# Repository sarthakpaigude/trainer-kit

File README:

This contains all Proteus and KiCad files for entire Project.

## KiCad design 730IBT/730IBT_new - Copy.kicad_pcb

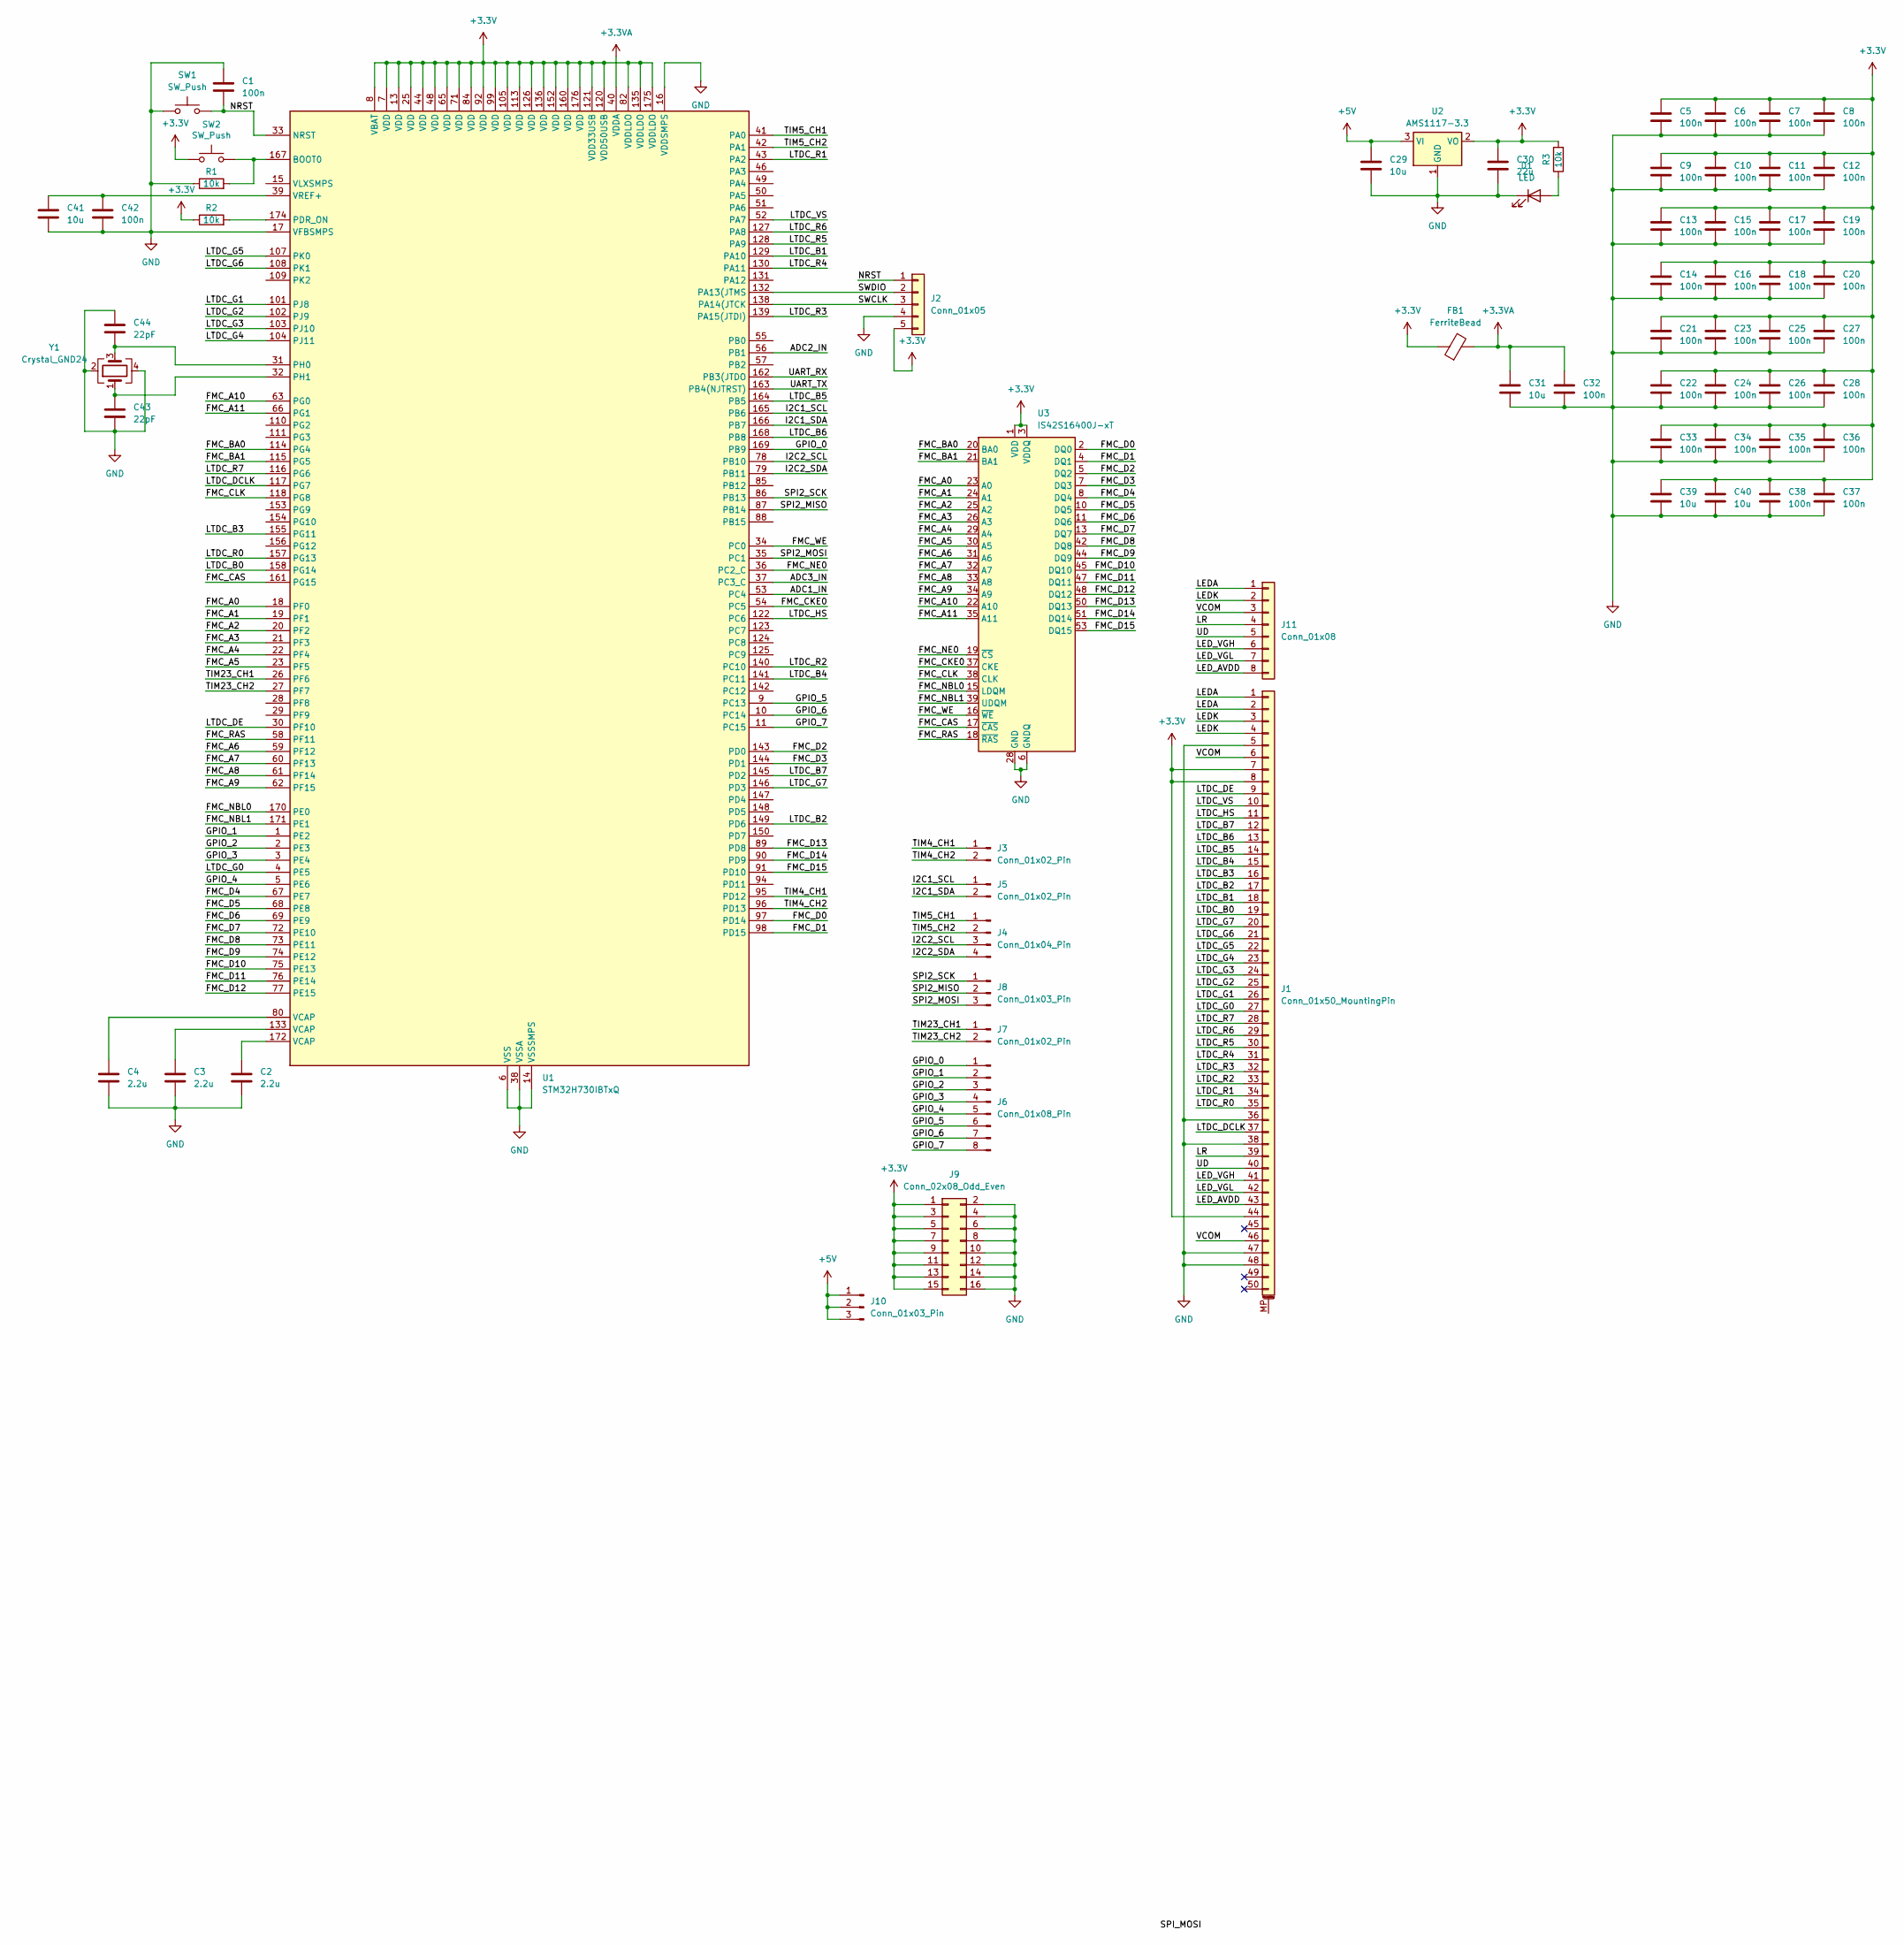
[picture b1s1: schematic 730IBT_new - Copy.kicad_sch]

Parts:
C1, C5, C6, C7, C8, C9, C10, C11, C12, C13, C14, C15, C16, C17, C18, C19, C20, C21, C22, C23, C24, C25, C26, C27, C28, C32, C33, C34, C35, C36, C37, C38, C42: 100n; C_0603_1608Metric_Pad1.08x0.95mm_HandSolder
C2, C3, C4: 2.2u; C_0603_1608Metric_Pad1.08x0.95mm_HandSolder
C29: 10u; C_0805_2012Metric_Pad1.18x1.45mm_HandSolder
C30: 22u; C_0805_2012Metric_Pad1.18x1.45mm_HandSolder
C31, C39, C40, C41: 10u; C_0603_1608Metric_Pad1.08x0.95mm_HandSolder
C43, C44: 22pF; C_0603_1608Metric_Pad1.08x0.95mm_HandSolder
D1: LED; LED_1206_3216Metric_Pad1.42x1.75mm_HandSolder
FB1: FerriteBead; L_0603_1608Metric_Pad1.05x0.95mm_HandSolder
J1: Conn_01x50_MountingPin; TE_5-1734839-0_1x50-1MP_P0.5mm_Horizontal
J2: Conn_01x05; PinSocket_1x05_P2.54mm_Vertical
J3, J5, J7: Conn_01x02_Pin; PinHeader_1x02_P2.54mm_Vertical
J4: Conn_01x04_Pin; PinHeader_1x04_P2.54mm_Vertical
J6: Conn_01x08_Pin; PinHeader_1x08_P2.54mm_Vertical
J8, J10: Conn_01x03_Pin; PinHeader_1x03_P2.54mm_Vertical
J9: Conn_02x08_Odd_Even; PinHeader_2x08_P2.54mm_Vertical
J11: Conn_01x08; PinHeader_1x08_P2.54mm_Vertical
R1, R2, R3: 10k; R_0603_1608Metric_Pad0.98x0.95mm_HandSolder
SW1, SW2: SW_Push; SW_Tactile_SPST_NO_Straight_CK_PTS636Sx25SMTRLFS
U1: STM32H730IBTxQ; LQFP-176_24x24mm_P0.5mm
U2: AMS1117-3.3; SOT-223-3_TabPin2
U3: IS42S16400J-xT; TSOP-II-54_22.2x10.16mm_P0.8mm
Y1: Crystal_GND24; Crystal_SMD_3225-4Pin_3.2x2.5mm

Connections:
+3.3V: C5.1, C6.1, C7.1, C8.1, C9.1, C10.1, C11.1, C12.1, C13.1, C14.1, C15.1, C16.1, C17.1, C18.1, C19.1, C20.1, C21.1, C22.1, C23.1, C24.1, C25.1, C26.1, C27.1, C28.1, C30.1, C33.1, C34.1, C35.1, C36.1, C37.1, C38.1, C39.1, C40.1, FB1.1, J1.7, J1.8, J1.44, J2.5, J9.1, J9.3, J9.5, J9.7, J9.9, J9.11, J9.13, J9.15, R2.1, R3.2, SW2.1, U1.7 (VDD), U1.8 (VBAT), U1.13 (VDD), U1.25 (VDD), U1.44 (VDD), U1.48 (VDD), U1.65 (VDD), U1.71 (VDD), U1.82 (VDDLDO), U1.84 (VDD), U1.92 (VDD), U1.99 (VDD), U1.105 (VDD), U1.113 (VDD), U1.120 (VDD50USB), U1.121 (VDD33USB), U1.126 (VDD), U1.135 (VDDLDO), U1.136 (VDD), U1.152 (VDD), U1.160 (VDD), U1.175 (VDDLDO), U1.176 (VDD), U2.2 (VO), U3.1 (VDD), U3.3 (VDDQ), U3.9 (VDDQ), U3.14 (VDD), U3.27 (VDD), U3.43 (VDDQ), U3.49 (VDDQ)
+3.3VA: C31.1, C32.1, FB1.2, U1.40 (VDDA)
+5V: C29.1, J10.1, J10.2, J10.3, U2.3 (VI)
/ADC1_IN: U1.53 (PC4)
/ADC2_IN: U1.56 (PB1)
/ADC3_IN: U1.37 (PC3_C)
/FMC_A0: U1.18 (PF0), U3.23 (A0)
/FMC_A1: U1.19 (PF1), U3.24 (A1)
/FMC_A2: U1.20 (PF2), U3.25 (A2)
/FMC_A3: U1.21 (PF3), U3.26 (A3)
/FMC_A4: U1.22 (PF4), U3.29 (A4)
/FMC_A5: U1.23 (PF5), U3.30 (A5)
/FMC_A6: U1.59 (PF12), U3.31 (A6)
/FMC_A7: U1.60 (PF13), U3.32 (A7)
/FMC_A8: U1.61 (PF14), U3.33 (A8)
/FMC_A9: U1.62 (PF15), U3.34 (A9)
/FMC_A10: U1.63 (PG0), U3.22 (A10)
/FMC_A11: U1.66 (PG1), U3.35 (A11)
/FMC_BA0: U1.114 (PG4), U3.20 (BA0)
/FMC_BA1: U1.115 (PG5), U3.21 (BA1)
/FMC_CAS: U1.161 (PG15), U3.17 (~CAS)
/FMC_CKE0: U1.54 (PC5), U3.37 (CKE)
/FMC_CLK: U1.118 (PG8), U3.38 (CLK)
/FMC_D0: U1.97 (PD14), U3.2 (DQ0)
/FMC_D1: U1.98 (PD15), U3.4 (DQ1)
/FMC_D2: U1.143 (PD0), U3.5 (DQ2)
/FMC_D3: U1.144 (PD1), U3.7 (DQ3)
/FMC_D4: U1.67 (PE7), U3.8 (DQ4)
/FMC_D5: U1.68 (PE8), U3.10 (DQ5)
/FMC_D6: U1.69 (PE9), U3.11 (DQ6)
/FMC_D7: U1.72 (PE10), U3.13 (DQ7)
/FMC_D8: U1.73 (PE11), U3.42 (DQ8)
/FMC_D9: U1.74 (PE12), U3.44 (DQ9)
/FMC_D10: U1.75 (PE13), U3.45 (DQ10)
/FMC_D11: U1.76 (PE14), U3.47 (DQ11)
/FMC_D12: U1.77 (PE15), U3.48 (DQ12)
/FMC_D13: U1.89 (PD8), U3.50 (DQ13)
/FMC_D14: U1.90 (PD9), U3.51 (DQ14)
/FMC_D15: U1.91 (PD10), U3.53 (DQ15)
/FMC_NBL0: U1.170 (PE0), U3.15 (LDQM)
/FMC_NBL1: U1.171 (PE1), U3.39 (UDQM)
/FMC_NE0: U1.36 (PC2_C), U3.19 (~CS)
/FMC_RAS: U1.58 (PF11), U3.18 (~RAS)
/FMC_WE: U1.34 (PC0), U3.16 (~WE)
/GPIO_0: J6.1, U1.169 (PB9)
/GPIO_1: J6.2, U1.1 (PE2)
/GPIO_2: J6.3, U1.2 (PE3)
/GPIO_3: J6.4, U1.3 (PE4)
/GPIO_4: J6.5, U1.5 (PE6)
/GPIO_5: J6.6, U1.9 (PC13)
/GPIO_6: J6.7, U1.10 (PC14)
/GPIO_7: J6.8, U1.11 (PC15)
/I2C1_SCL: J5.1, U1.165 (PB6)
/I2C1_SDA: J5.2, U1.166 (PB7)
/I2C2_SCL: J4.3, U1.78 (PB10)
/I2C2_SDA: J4.4, U1.79 (PB11)
/LEDA: J1.1, J1.2, J11.1
/LEDK: J1.3, J1.4, J11.2
/LED_AVDD: J1.43, J11.8
/LED_VGH: J1.41, J11.6
/LED_VGL: J1.42, J11.7
/LR: J1.39, J11.4
/LTDC_B0: J1.19, U1.158 (PG14)
/LTDC_B1: J1.18, U1.129 (PA10)
/LTDC_B2: J1.17, U1.149 (PD6)
/LTDC_B3: J1.16, U1.155 (PG11)
/LTDC_B4: J1.15, U1.141 (PC11)
/LTDC_B5: J1.14, U1.164 (PB5)
/LTDC_B6: J1.13, U1.168 (PB8)
/LTDC_B7: J1.12, U1.145 (PD2)
/LTDC_DCLK: J1.37, U1.117 (PG7)
/LTDC_DE: J1.9, U1.30 (PF10)
/LTDC_G0: J1.27, U1.4 (PE5)
/LTDC_G1: J1.26, U1.101 (PJ8)
/LTDC_G2: J1.25, U1.102 (PJ9)
/LTDC_G3: J1.24, U1.103 (PJ10)
/LTDC_G4: J1.23, U1.104 (PJ11)
/LTDC_G5: J1.22, U1.107 (PK0)
/LTDC_G6: J1.21, U1.108 (PK1)
/LTDC_G7: J1.20, U1.146 (PD3)
/LTDC_HS: J1.11, U1.122 (PC6)
/LTDC_R0: J1.35, U1.157 (PG13)
/LTDC_R1: J1.34, U1.43 (PA2)
/LTDC_R2: J1.33, U1.140 (PC10)
/LTDC_R3: J1.32, U1.139 (PA15(JTDI))
/LTDC_R4: J1.31, U1.130 (PA11)
/LTDC_R5: J1.30, U1.128 (PA9)
/LTDC_R6: J1.29, U1.127 (PA8)
/LTDC_R7: J1.28, U1.116 (PG6)
/LTDC_VS: J1.10, U1.52 (PA7)
/NRST: C1.2, J2.1, SW1.2, U1.33 (NRST)
/SPI2_MISO: J8.2, U1.87 (PB14)
/SPI2_MOSI: J8.3, U1.35 (PC1)
/SPI2_SCK: J8.1, U1.86 (PB13)
/TIM4_CH1: J3.1, U1.95 (PD12)
/TIM4_CH2: J3.2, U1.96 (PD13)
/TIM5_CH1: J4.1, U1.41 (PA0)
/TIM5_CH2: J4.2, U1.42 (PA1)
/TIM23_CH1: J7.1, U1.26 (PF6)
/TIM23_CH2: J7.2, U1.27 (PF7)
/UART_RX: U1.162 (PB3(JTDO)
/UART_TX: U1.163 (PB4(NJTRST))
/UD: J1.40, J11.5
/VCOM: J1.6, J1.46, J11.3
GND: C1.1, C2.2, C3.2, C4.2, C5.2, C6.2, C7.2, C8.2, C9.2, C10.2, C11.2, C12.2, C13.2, C14.2, C15.2, C16.2, C17.2, C18.2, C19.2, C20.2, C21.2, C22.2, C23.2, C24.2, C25.2, C26.2, C27.2, C28.2, C29.2, C30.2, C31.2, C32.2, C33.2, C34.2, C35.2, C36.2, C37.2, C38.2, C39.2, C40.2, C41.2, C42.2, C43.2, C44.1, D1.1 (K), J1.5, J1.36, J1.38, J1.47, J1.48, J2.4, J9.2, J9.4, J9.6, J9.8, J9.10, J9.12, J9.14, J9.16, R1.1, SW1.1, U1.6 (VSS), U1.12 (VSS), U1.14 (VSSSMPS), U1.16 (VDDSMPS), U1.17 (VFBSMPS), U1.24 (VSS), U1.38 (VSSA), U1.45 (VSS), U1.47 (VSS), U1.64 (VSS), U1.70 (VSS), U1.81 (VSS), U1.83 (VSS), U1.93 (VSS), U1.100 (VSS), U1.106 (VSS), U1.112 (VSS), U1.119 (VSS), U1.134 (VSS), U1.137 (VSS), U1.151 (VSS), U1.159 (VSS), U1.173 (VSS), U2.1 (GND), U3.6 (GNDQ), U3.12 (GNDQ), U3.28 (GND), U3.41 (GND), U3.46 (GNDQ), U3.52 (GNDQ), U3.54 (GND), Y1.2, Y1.4
unnamed: C2.1, U1.172 (VCAP)
unnamed: C3.1, U1.133 (VCAP)
unnamed: C4.1, U1.80 (VCAP)
unnamed: D1.2 (A), R3.1
unnamed: J2.2, U1.132 (PA13(JTMS)
unnamed: J2.3, U1.138 (PA14(JTCK)
unnamed: R1.2, SW2.2, U1.167 (BOOT0)
unnamed: R2.2, U1.174 (PDR_ON)
unnamed: C44.2, U1.31 (PH0), Y1.3
unnamed: C43.1, U1.32 (PH1), Y1.1
unnamed: C41.1, C42.1, U1.39 (VREF+)

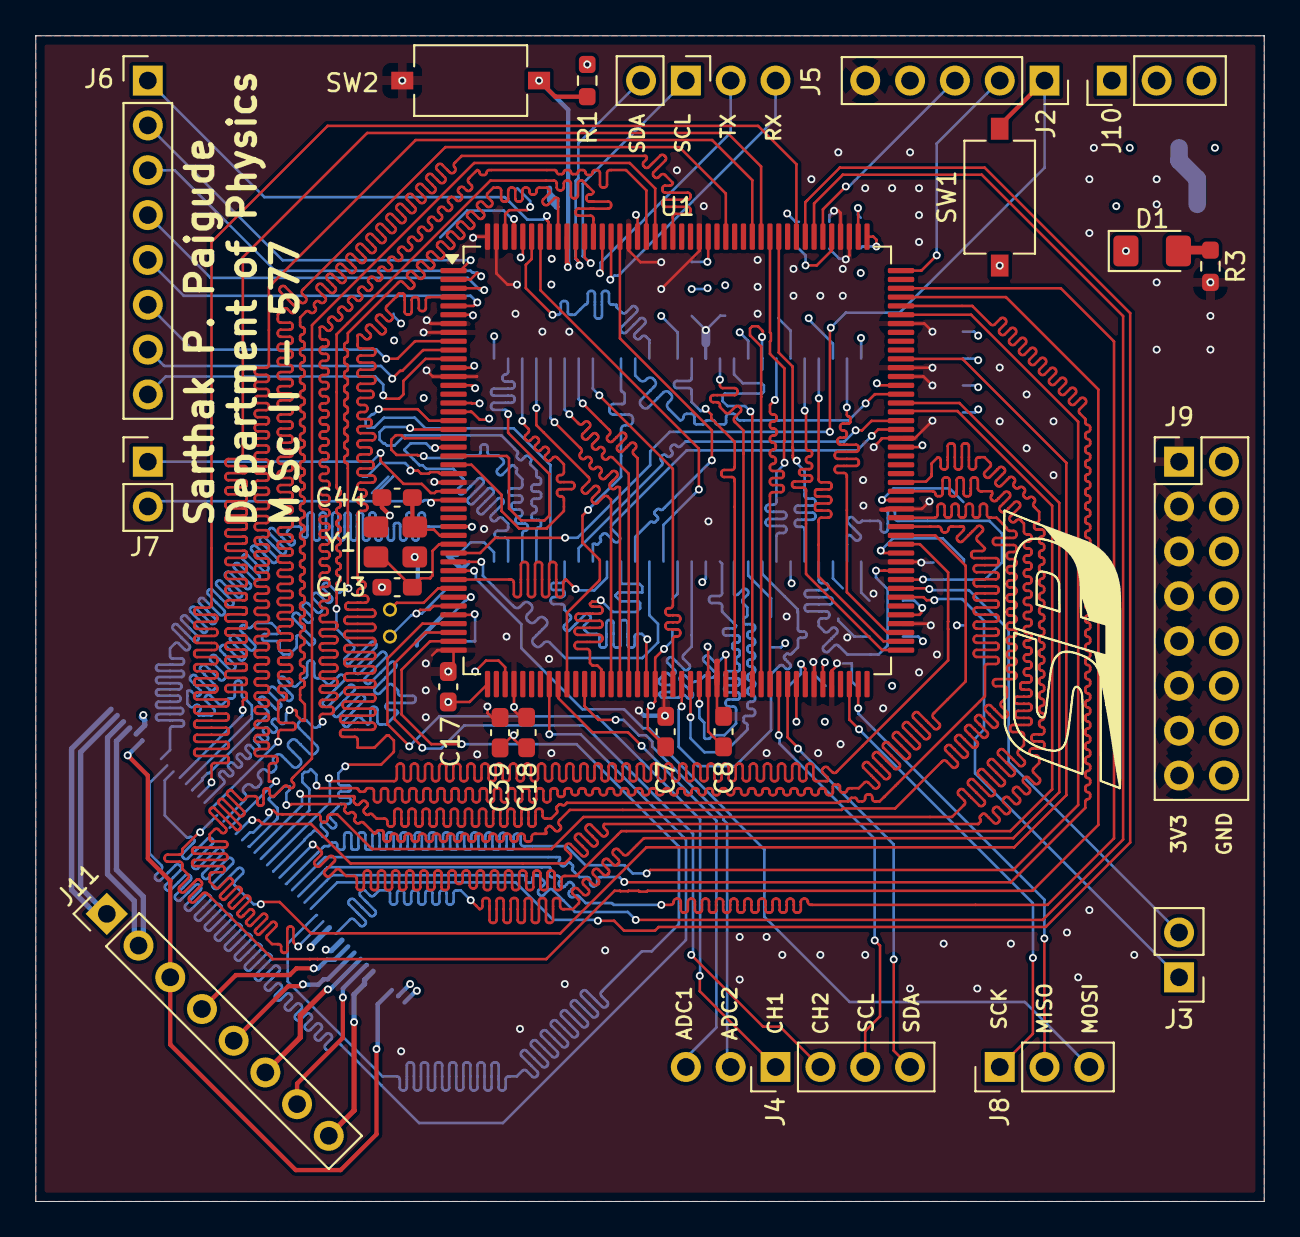
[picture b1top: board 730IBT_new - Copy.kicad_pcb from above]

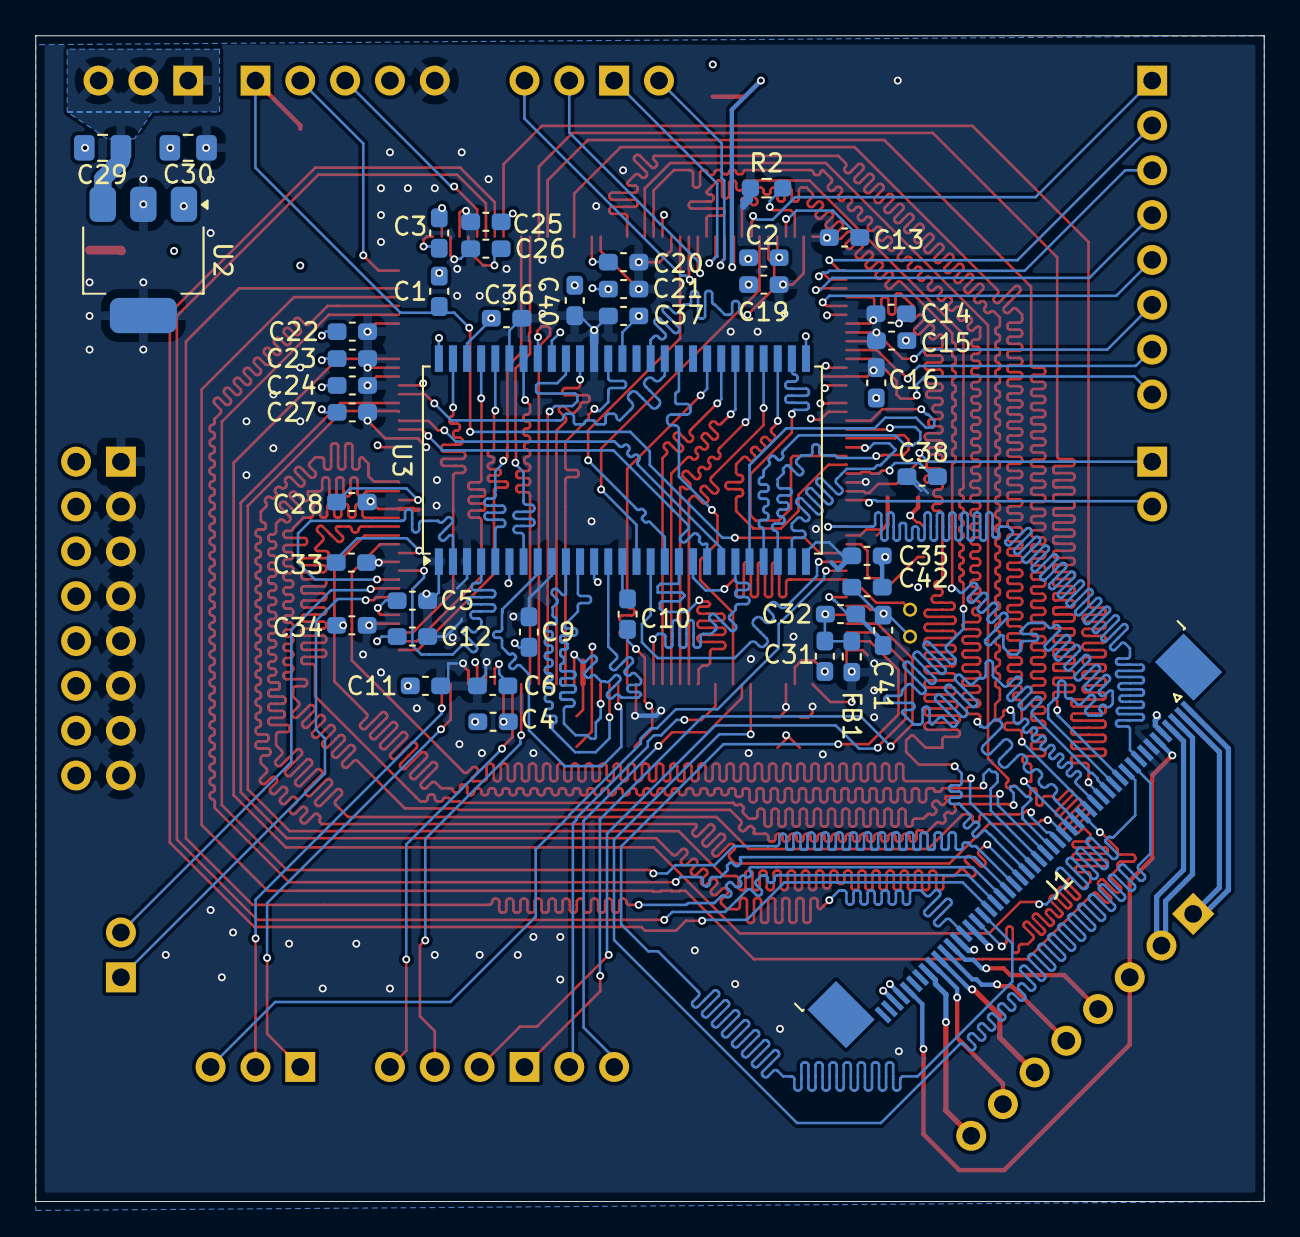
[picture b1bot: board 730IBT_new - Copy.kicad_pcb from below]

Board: 4 copper layers, 69.6 x 66.0 mm, 66 parts (42 on the bottom side), 111 nets.

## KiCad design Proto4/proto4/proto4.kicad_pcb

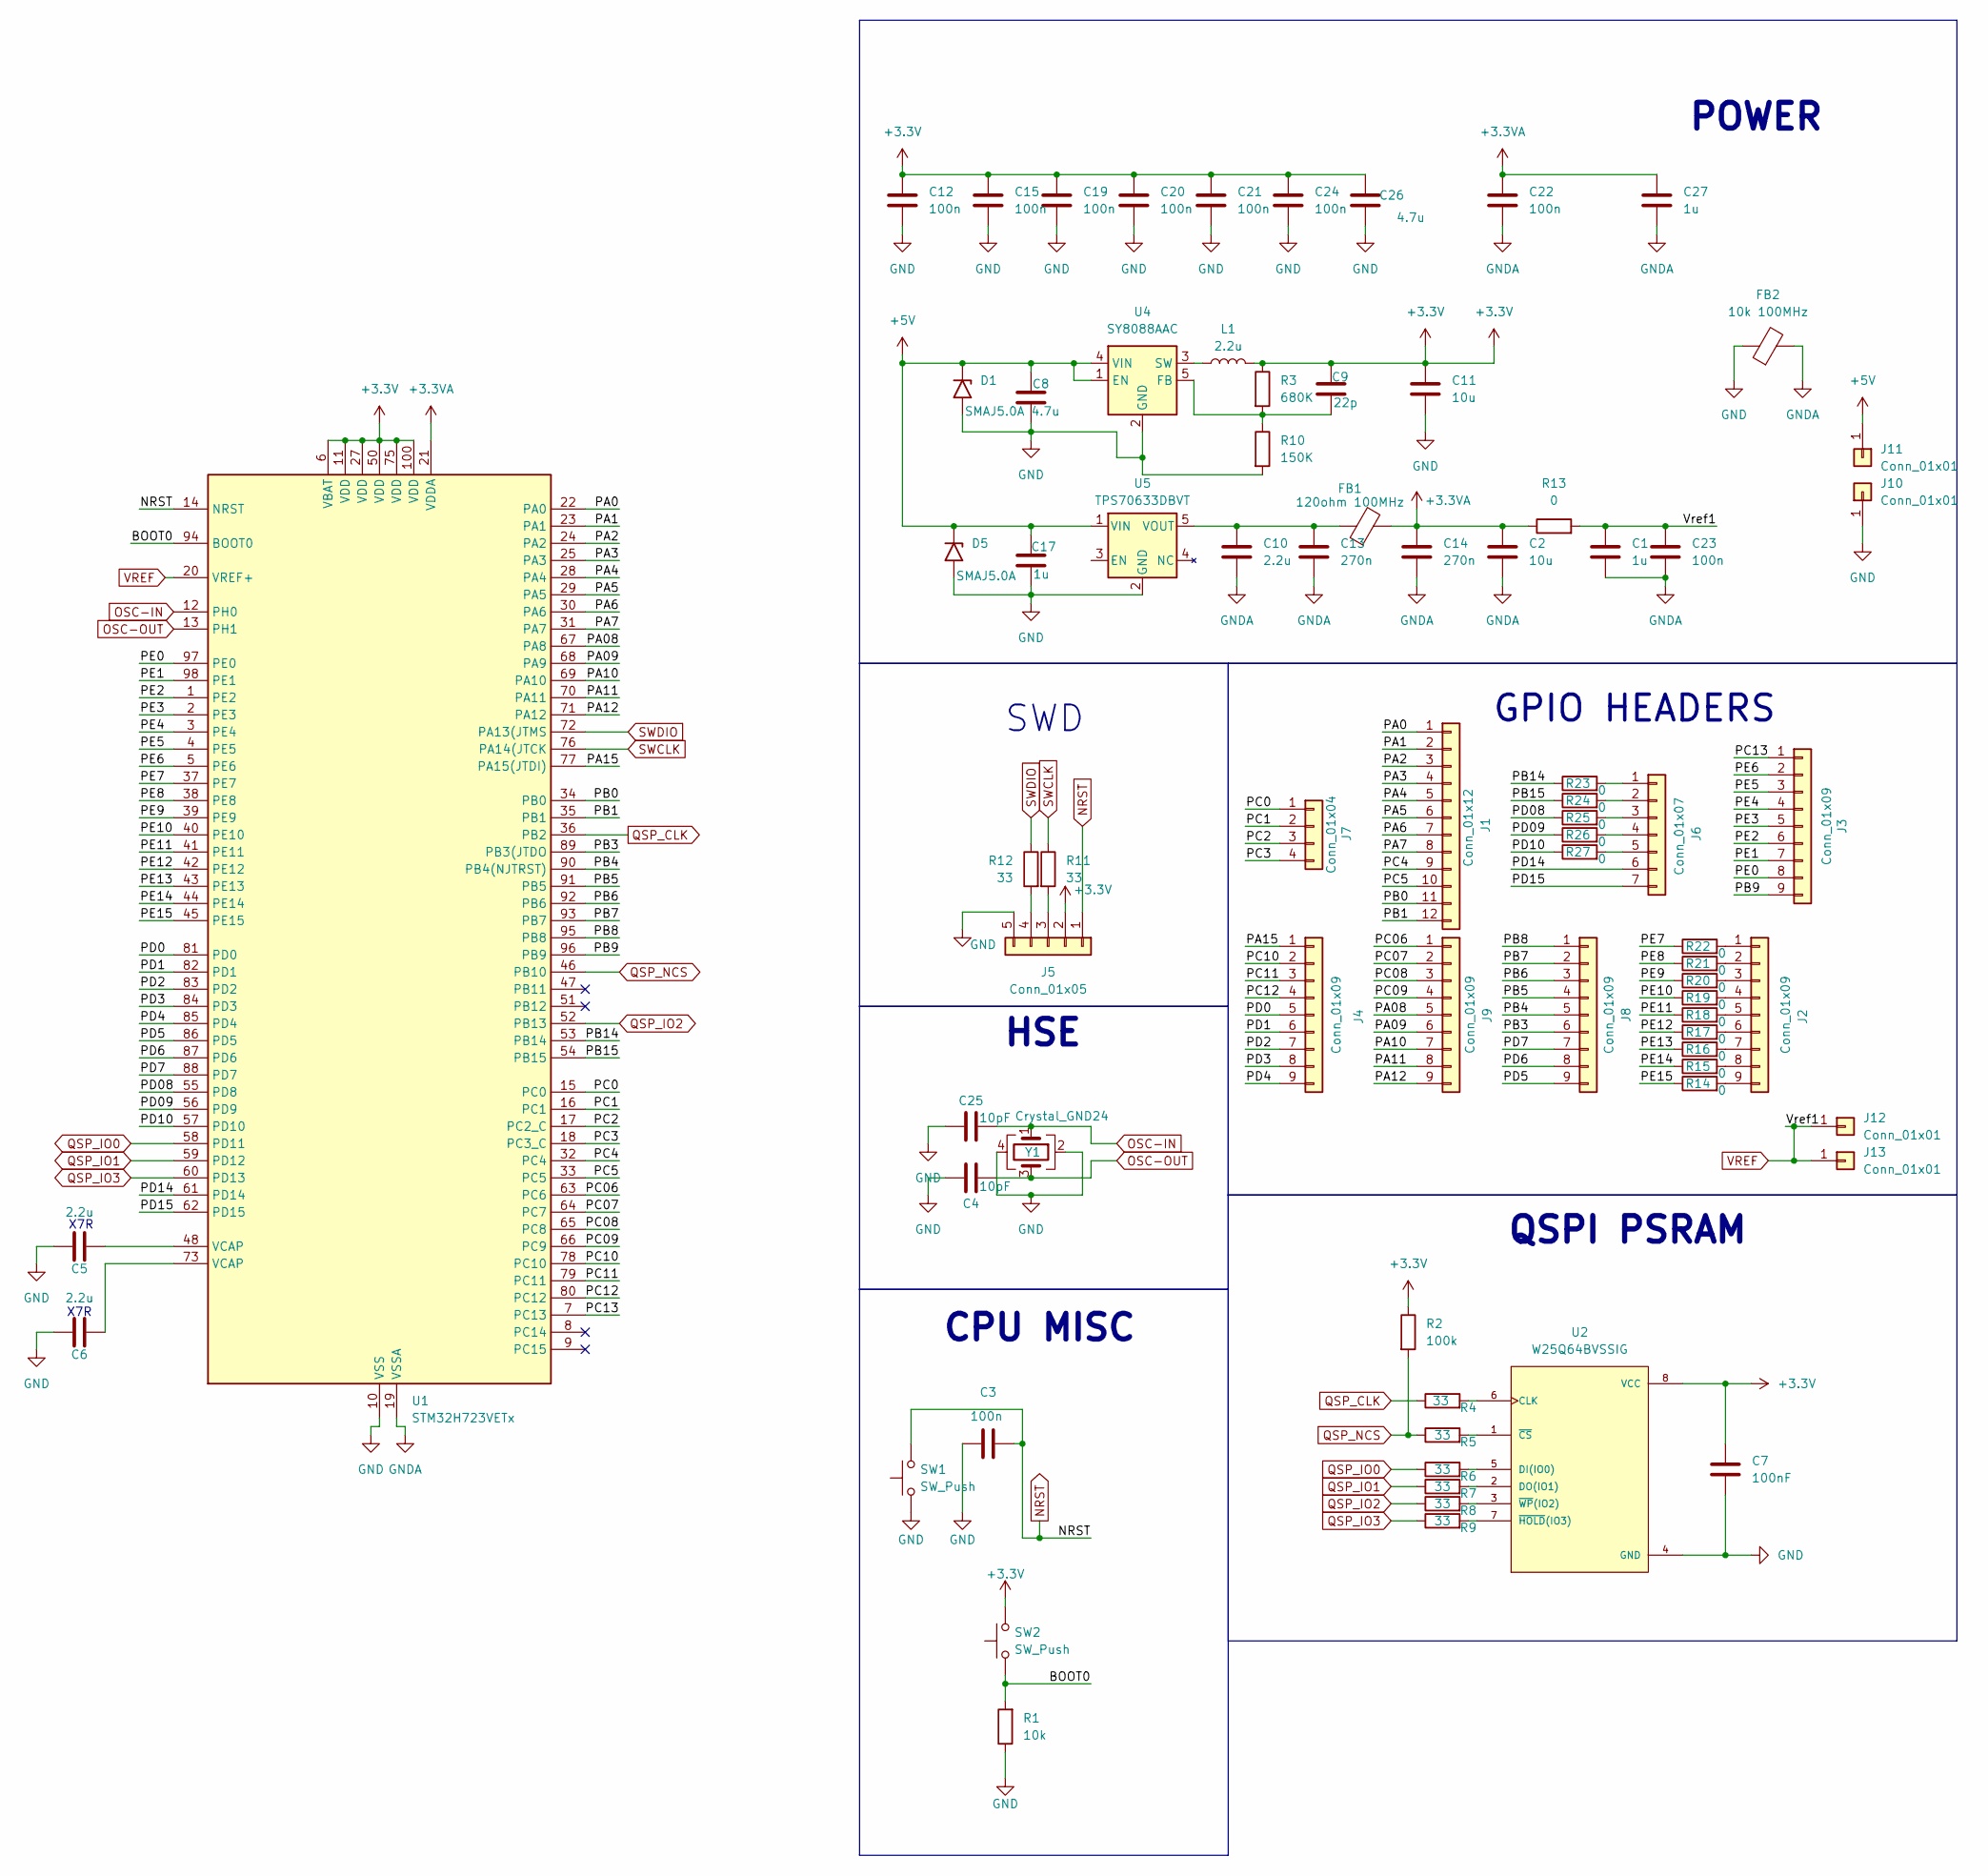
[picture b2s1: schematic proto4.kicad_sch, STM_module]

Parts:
C1, C17, C27: 1u; C_0805_2012Metric_Pad1.18x1.45mm_HandSolder
C2, C11: 10u; C_0805_2012Metric_Pad1.18x1.45mm_HandSolder
C3, C12, C15, C19, C20, C21, C22, C23, C24: 100n; C_0805_2012Metric_Pad1.18x1.45mm_HandSolder
C4, C25: 10pF; C_0805_2012Metric_Pad1.18x1.45mm_HandSolder
C5, C6, C10: 2.2u; C_0805_2012Metric_Pad1.18x1.45mm_HandSolder
C7: 100nF; C_0805_2012Metric_Pad1.18x1.45mm_HandSolder
C8, C26: 4.7u; C_0805_2012Metric_Pad1.18x1.45mm_HandSolder
C9: 22p; C_0805_2012Metric_Pad1.18x1.45mm_HandSolder
C13, C14: 270n; C_0805_2012Metric_Pad1.18x1.45mm_HandSolder
D1, D5: SMAJ5.0A; D_SMA
FB1: 120ohm 100MHz; L_0805_2012Metric_Pad1.15x1.40mm_HandSolder
FB2: 10k 100MHz; L_0805_2012Metric
J1: Conn_01x12; PinHeader_1x12_P2.54mm_Vertical
J2, J3, J4, J8, J9: Conn_01x09; PinHeader_1x09_P2.54mm_Vertical
J5: Conn_01x05; PinHeader_1x05_P2.54mm_Horizontal
J6: Conn_01x07; PinHeader_1x07_P2.54mm_Vertical
J7: Conn_01x04; PinHeader_1x04_P2.54mm_Vertical
J10, J11: Conn_01x01; PinHeader_1x01_P2.54mm_Horizontal
J12, J13: Conn_01x01; PinHeader_1x01_P2.54mm_Vertical
L1: 2.2u; L_0805_2012Metric_Pad1.15x1.40mm_HandSolder
R1: 10k; R_0805_2012Metric_Pad1.20x1.40mm_HandSolder
R2: 100k; R_0805_2012Metric_Pad1.20x1.40mm_HandSolder
R3: 680K; R_0805_2012Metric_Pad1.20x1.40mm_HandSolder
R4, R5, R6, R7, R8, R9, R11, R12: 33; R_0805_2012Metric_Pad1.20x1.40mm_HandSolder
R10: 150K; R_0805_2012Metric_Pad1.20x1.40mm_HandSolder
R13, R14, R15, R16, R17, R18, R19, R20, R21, R22: 0; R_0603_1608Metric
R23, R24, R25, R26, R27: 0; R_1206_3216Metric_Pad1.30x1.75mm_HandSolder
SW1, SW2: SW_Push; SW_PUSH_6mm
U1: STM32H723VETx; LQFP-100_14x14mm_P0.5mm
U2: W25Q64BVSSIG; SOIC127P790X216-8N
U4: SY8088AAC; SOT-23-5
U5: TPS70633DBVT; SOT-23-5
Y1: Crystal_GND24; Crystal_SMD_EuroQuartz_MT-4Pin_3.2x2.5mm_HandSoldering

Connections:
+3.3V: C7.1, C9.1, C11.1, C12.1, C15.1, C19.1, C20.1, C21.1, C24.1, C26.1, J5.2, L1.2, R2.1, R3.1, SW2.2, U1.6 (VBAT), U1.11 (VDD), U1.27 (VDD), U1.50 (VDD), U1.75 (VDD), U1.100 (VDD), U2.8 (VCC)
+3.3VA: C2.1, C14.1, C22.1, C27.1, FB1.2, R13.1, U1.21 (VDDA)
+5V: C8.1, C17.1, D1.1 (A1), D5.1 (A1), J11.1, U4.1 (EN), U4.4 (VIN), U5.1 (VIN)
/BOOT0: R1.2, SW2.1, U1.94 (BOOT0)
/PA0: J1.1, U1.22 (PA0)
/PA1: J1.2, U1.23 (PA1)
/PA2: J1.3, U1.24 (PA2)
/PA3: J1.4, U1.25 (PA3)
/PA4: J1.5, U1.28 (PA4)
/PA5: J1.6, U1.29 (PA5)
/PA6: J1.7, U1.30 (PA6)
/PA7: J1.8, U1.31 (PA7)
/PA08: J9.5, U1.67 (PA8)
/PA09: J9.6, U1.68 (PA9)
/PA10: J9.7, U1.69 (PA10)
/PA11: J9.8, U1.70 (PA11)
/PA12: J9.9, U1.71 (PA12)
/PA15: J4.1, U1.77 (PA15(JTDI))
/PB0: J1.11, U1.34 (PB0)
/PB1: J1.12, U1.35 (PB1)
/PB3: J8.6, U1.89 (PB3(JTDO)
/PB4: J8.5, U1.90 (PB4(NJTRST))
/PB5: J8.4, U1.91 (PB5)
/PB6: J8.3, U1.92 (PB6)
/PB7: J8.2, U1.93 (PB7)
/PB8: J8.1, U1.95 (PB8)
/PB9: J3.9, U1.96 (PB9)
/PB14: R23.1, U1.53 (PB14)
/PB15: R24.1, U1.54 (PB15)
/PC0: J7.1, U1.15 (PC0)
/PC1: J7.2, U1.16 (PC1)
/PC2: J7.3, U1.17 (PC2_C)
/PC3: J7.4, U1.18 (PC3_C)
/PC4: J1.9, U1.32 (PC4)
/PC5: J1.10, U1.33 (PC5)
/PC06: J9.1, U1.63 (PC6)
/PC07: J9.2, U1.64 (PC7)
/PC08: J9.3, U1.65 (PC8)
/PC09: J9.4, U1.66 (PC9)
/PC10: J4.2, U1.78 (PC10)
/PC11: J4.3, U1.79 (PC11)
/PC12: J4.4, U1.80 (PC12)
/PC13: J3.1, U1.7 (PC13)
/PD0: J4.5, U1.81 (PD0)
/PD1: J4.6, U1.82 (PD1)
/PD2: J4.7, U1.83 (PD2)
/PD3: J4.8, U1.84 (PD3)
/PD4: J4.9, U1.85 (PD4)
/PD5: J8.9, U1.86 (PD5)
/PD6: J8.8, U1.87 (PD6)
/PD7: J8.7, U1.88 (PD7)
/PD08: R25.1, U1.55 (PD8)
/PD09: R26.1, U1.56 (PD9)
/PD10: R27.1, U1.57 (PD10)
/PD14: J6.6, U1.61 (PD14)
/PD15: J6.7, U1.62 (PD15)
/PE0: J3.8, U1.97 (PE0)
/PE1: J3.7, U1.98 (PE1)
/PE2: J3.6, U1.1 (PE2)
/PE3: J3.5, U1.2 (PE3)
/PE4: J3.4, U1.3 (PE4)
/PE5: J3.3, U1.4 (PE5)
/PE6: J3.2, U1.5 (PE6)
/PE7: R22.1, U1.37 (PE7)
/PE8: R21.1, U1.38 (PE8)
/PE9: R20.1, U1.39 (PE9)
/PE10: R19.1, U1.40 (PE10)
/PE11: R18.1, U1.41 (PE11)
/PE12: R17.1, U1.42 (PE12)
/PE13: R16.1, U1.43 (PE13)
/PE14: R15.1, U1.44 (PE14)
/PE15: R14.1, U1.45 (PE15)
GND: C3.2, C4.1, C5.1, C6.1, C7.2, C8.2, C11.2, C12.2, C15.2, C17.2, C19.2, C20.2, C21.2, C24.2, C25.1, C26.2, D1.2 (A2), D5.2 (A2), FB2.1, J5.5, J10.1, R1.1, R10.2, SW1.1, U1.10 (VSS), U1.26 (VSS), U1.49 (VSS), U1.74 (VSS), U1.99 (VSS), U2.4 (GND), U4.2 (GND), U5.2 (GND), Y1.2, Y1.4
GNDA: C1.2, C2.2, C10.2, C13.2, C14.2, C22.2, C23.2, C27.2, FB2.2, U1.19 (VSSA)
NRST: C3.1, J5.1, SW1.2, U1.14 (NRST)
unnamed: C5.2, U1.48 (VCAP)
unnamed: C6.2, U1.73 (VCAP)
unnamed: J2.1, R22.2
unnamed: J2.2, R21.2
unnamed: J2.3, R20.2
unnamed: J2.4, R19.2
unnamed: J2.5, R18.2
unnamed: J2.6, R17.2
unnamed: J2.7, R16.2
unnamed: J2.8, R15.2
unnamed: J2.9, R14.2
unnamed: J5.3, R11.2
unnamed: J5.4, R12.2
unnamed: J6.1, R23.2
unnamed: J6.2, R24.2
unnamed: J6.3, R25.2
unnamed: J6.4, R26.2
unnamed: J6.5, R27.2
unnamed: R4.2, U2.6 (CLK)
unnamed: R6.2, U2.5 (DI(IO0))
unnamed: R7.2, U2.2 (DO(IO1))
unnamed: R5.2, U2.1 (~CS)
unnamed: R9.2, U2.7 (~HOLD(IO3))
unnamed: R8.2, U2.3 (~WP(IO2))
unnamed: C9.2, R3.2, R10.1, U4.5 (FB)
unnamed: L1.1, U4.3 (SW)
unnamed: C10.1, C13.1, FB1.1, U5.5 (VOUT)
OSC-IN: C25.2, U1.12 (PH0), Y1.1
OSC-OUT: C4.2, U1.13 (PH1), Y1.3
QSP_CLK: R4.1, U1.36 (PB2)
QSP_IO0: R6.1, U1.58 (PD11)
QSP_IO1: R7.1, U1.59 (PD12)
QSP_IO2: R8.1, U1.52 (PB13)
QSP_IO3: R9.1, U1.60 (PD13)
QSP_NCS: R2.2, R5.1, U1.46 (PB10)
SWCLK: R11.1, U1.76 (PA14(JTCK)
SWDIO: R12.1, U1.72 (PA13(JTMS)
VREF: C1.1, C23.1, J12.1, J13.1, R13.2, U1.20 (VREF+)

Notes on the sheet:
SWD
X7R
CPU MISC
HSE
POWER
GPIO HEADERS
QSPI PSRAM

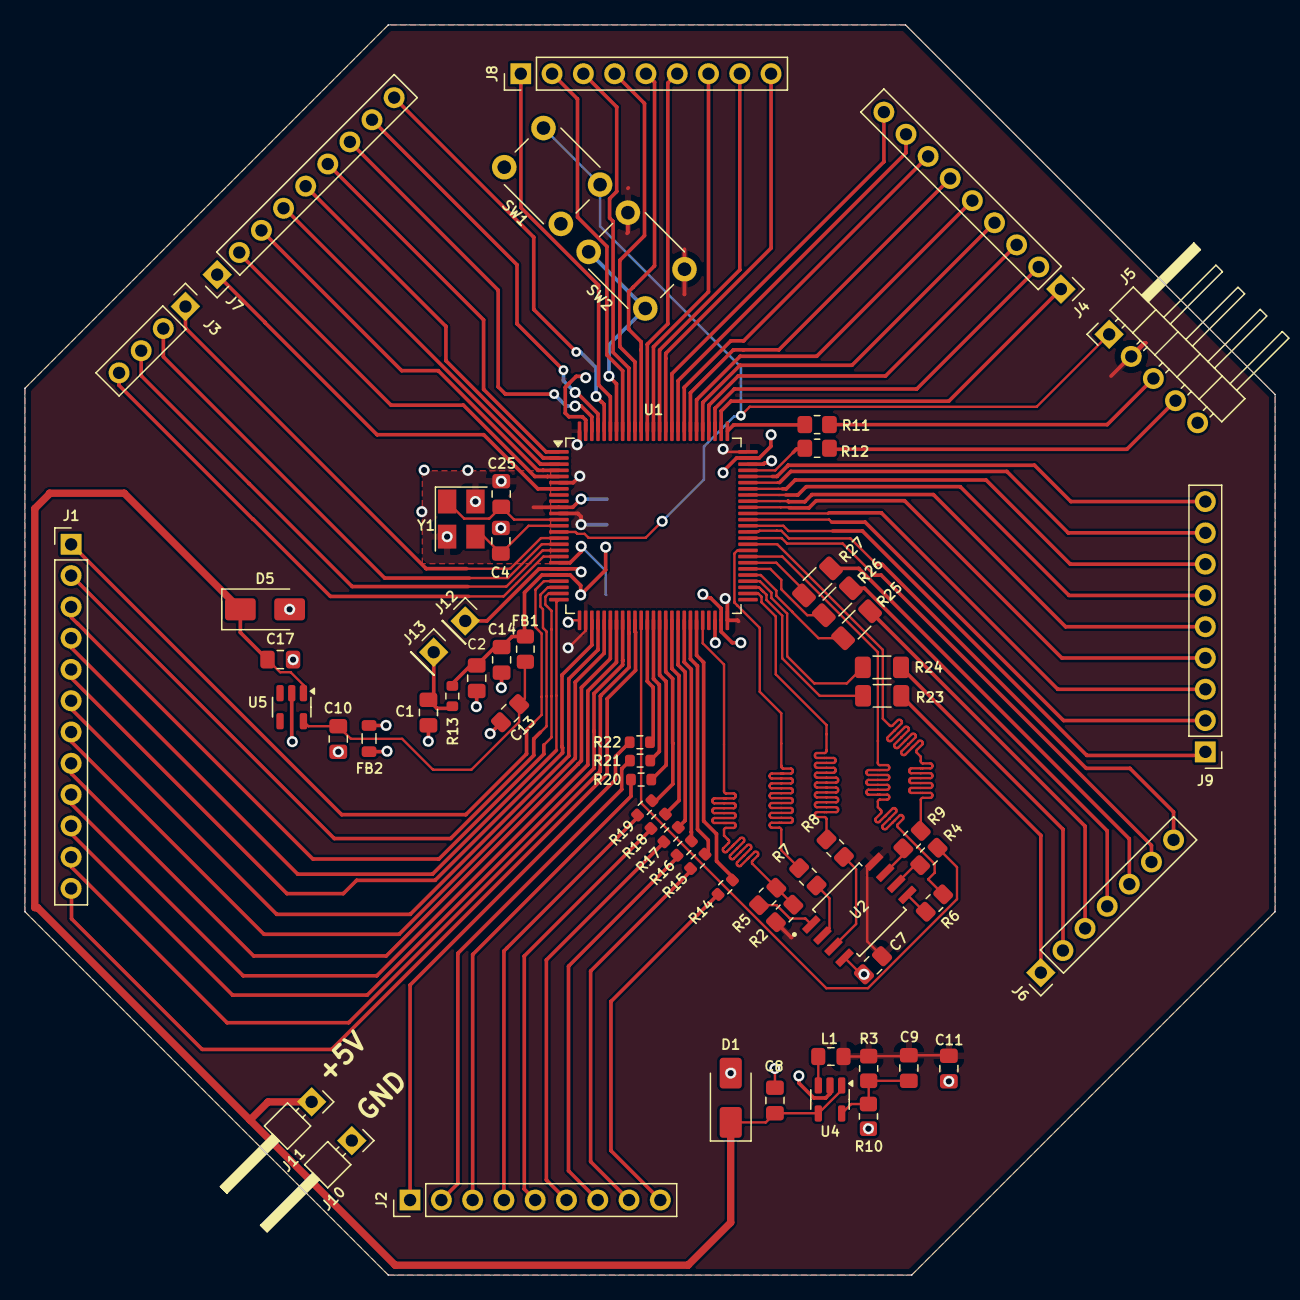
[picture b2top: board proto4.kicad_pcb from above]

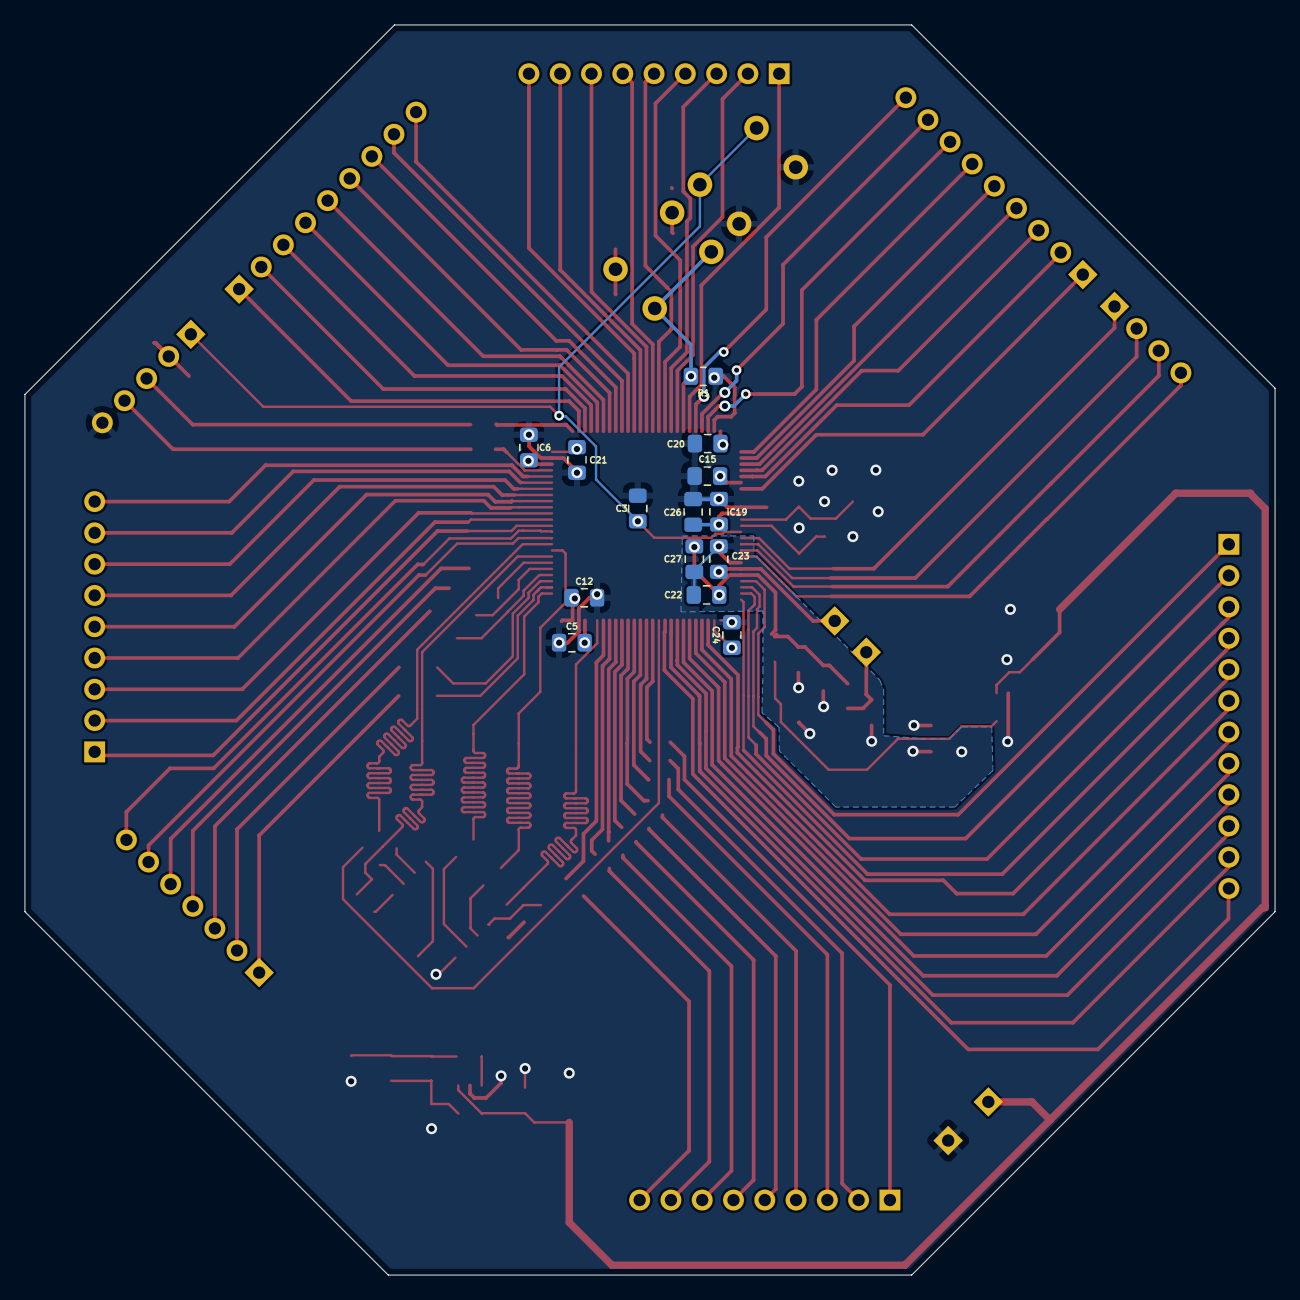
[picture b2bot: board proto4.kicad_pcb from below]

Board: 2 copper layers, 101.5 x 101.5 mm, 77 parts (14 on the bottom side), 113 nets.
